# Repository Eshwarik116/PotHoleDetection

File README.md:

# Intelligent Pothole Detection System (IPDS)

An advanced IoT and AI-powered solution for real-time road hazard assessment using a dual ESP32 architecture and YOLOv8 object detection.

---

## Problem Statement
Poorly maintained roads and unexpected potholes cause severe vehicle damage and contribute to thousands of traffic accidents annually. Current road inspection methods rely heavily on slow, manual reporting by citizens or municipal workers, leaving prolonged periods where hazardous road conditions go unaddressed.

## Solution Overview
The IPDS project solves this by automating road quality assessment. By mounting a camera and accelerometer setup on a vehicle, the system continuously scans the road ahead. When the computer vision model detects a pothole, it triangulates that visual data with physical vibration data (jerk) captured as the vehicle drives over it. This creates a highly accurate, geo-tagged "Severity Score" for every pothole, ready to be mapped and prioritized by road maintenance authorities.

## Key Features
- **Real-time Pothole Detection:** Powered by a custom-trained YOLOv8 model.
- **Multi-Object Tracking:** Uses the SORT algorithm to prevent duplicate counting of the same pothole across frames.
- **Vehicle Vibration Sensing:** MPU6050 accelerometer accurately measures the physical depth/impact of the pothole.
- **GPS Location Tagging:** Automatically records the exact latitude and longitude of hazards.
- **Sensor Fusion Severity Scoring:** Combines AI visual confidence with physical impact data to rank pothole severity.
- **Smart Data Logging:** Outputs clean, Firebase-ready CSV logs.

---

## System Overview (High Level)
The system operates on an **Event-Driven Dual ESP32 Architecture**. 
1. The **ESP32-CAM** continuously streams video to a central Python processing hub.
2. The Python hub runs **YOLOv8** to visually detect potholes.
3. Upon confirming a valid pothole, Python sends a query to the **ESP32 Sensor Node**.
4. The Sensor Node responds with physical accelerometer, GPS, and RTC data.
5. The system calculates a combined severity score and logs the data.

## Hardware Used
- **Vision Node:** ESP32-CAM + OV2640 Module
- **Sensor Node:** ESP32 Dev Board
- **Accelerometer:** MPU6050 (6-axis motion tracking)
- **GPS Module:** NEO-6M
- **Real-Time Clock:** DS3231 RTC
- **Processing Hub:** Laptop or Edge Computer (e.g., Jetson Nano)

## Software Stack
- **Python 3.10+** (Core processing logic)
- **OpenCV** (Image processing and video stream handling)
- **Ultralytics YOLOv8** (Computer Vision / Object Detection)
- **FilterPy / SciPy** (SORT tracking algorithm)
- **C++ / Arduino Framework** (ESP32 Firmware)

---

## Project Structure
```text
Pot Hole Detection/
├── .env                             # Centralized WiFi credentials
├── README.md                        # This file
├── update_wifi.py                   # Script to inject WiFi credentials to C++
├── requirements.txt                 # Python dependencies
├── python/                          
│   ├── main.py                      # Main AI & Processing entry point
│   └── pothole_detection/           # SORT and YOLO wrapper modules
├── ESP_32_Code/                        
│   ├── esp_32_cam_final/            # ESP32-CAM firmware (Vision Node)
│   └── esp_32_final/                # ESP32 Sensor firmware (Sensor Node)
├── assets/
│   └── models/                      # Trained YOLOv8 model (.pt)
├── outputs/                         # Generated CSV logs and annotated videos
└── docs/                            # Deep technical documentation
```

---

## Installation & Setup Instructions

### 1. Hardware Configuration
1. Open the `.env` file in the root directory and update it with your WiFi Hotspot's SSID and Password. All devices *must* share the same network.
2. Run `python update_wifi.py` to sync these credentials to the ESP32 code.
3. Flash `ESP_32_Code/esp_32_cam_final/esp_32_cam_final.ino` to your ESP32-CAM. Monitor the Serial output to get its IP address.
4. Flash `ESP_32_Code/esp_32_final/esp_32_final.ino` to your ESP32 Sensor Node. Monitor the Serial output to get its IP address.

### 2. Software Configuration
1. Install dependencies: `pip install -r requirements.txt`
2. Open `python/main.py`.
3. Locate the `ESP32_CAM_IP` and `ESP32_SENSOR_IP` variables at the top of the file. Update them with the IPs you retrieved from the hardware step.

## Usage
To start the live tracking and detection system, simply run:
```bash
python python/main.py
```
A video window will open showing the live feed with bounding boxes and tracking IDs. Press `q` to safely terminate the program. All reports will be saved in the `outputs/logs/` directory.

---

## Future Scope
- **Dashcam Integration:** Utilize ubiquitous vehicle dashcams and smartphone apps to passively crowdsource road condition data without custom hardware.
- **System Scalability:** Migrate processing to distributed cloud infrastructure (AWS/GCP) using microservices and Kubernetes to handle millions of edge devices.
- **Government Portals:** Provide secure web dashboards for municipal bodies featuring real-time heatmaps and predictive analytics for budget allocation.
- **Navigational Alerts:** Integrate with OpenStreetMap (OSM) to issue proactive audio/visual warnings to drivers about upcoming road hazards.
- **Spatial Database:** Store detections in a highly optimized database (e.g., PostgreSQL with PostGIS) and expose REST APIs for researchers and self-driving models.
- **Advanced Sensor Integration:** Incorporate LiDAR or Thermal/Infrared cameras for 24/7 visibility regardless of weather, glare, or darkness.
- **Predictive Maintenance:** Analyze micro-cracks and freeze-thaw weather patterns to predict and map impending road failures before physical potholes form.
- **V2X Communication:** Broadcast real-time hazard coordinates to trailing autonomous vehicles so they can automatically steer around or brace for impact.
- **Automated Work-Orders:** Integrate strictly with City ERP software to automatically dispatch repair crews and calculate necessary asphalt volumes for severe hazards.
- **True Edge Acceleration:** Utilize dedicated AI ASICs (like Google Coral TPU or Hailo-8) to run the entire YOLO pipeline locally without needing a laptop.
- **Crowdsourcing Incentives:** Implement gamified "micro-bounties" (e.g., toll credits or tax rebates) to incentivize citizens to run the detection app while commuting.

## Contributors
- **Sanskar Tiwari** - *Core Architecture & ML Pipeline*

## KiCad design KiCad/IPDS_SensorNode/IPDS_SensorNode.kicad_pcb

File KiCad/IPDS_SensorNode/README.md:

# IPDS Sensor Node — KiCad PCB Project

**KiCad Version:** 7.x  
**Board:** 120 × 90 mm · FR4 · 1.6 mm · 2 layers · HASL · 1 oz copper

---

## Files in This Project

| File | Description |
|---|---|
| `IPDS_SensorNode.kicad_pro` | KiCad project settings & DRC rules |
| `IPDS_SensorNode.kicad_sch` | Full schematic — all components & nets |
| `IPDS_SensorNode.kicad_pcb` | PCB layout — footprints, traces, GND plane |
| `sym-lib-table` | Symbol library references |
| `fp-lib-table` | Footprint library references |

---

## How to Open

1. Install **KiCad 7** (https://www.kicad.org/download/)
2. Open `IPDS_SensorNode.kicad_pro` — KiCad will load the project
3. Open **Schematic Editor** (Eeschema) to view the schematic
4. Open **PCB Editor** (PcbNew) to view and edit the PCB layout

---

## Design Overview

### Components

| Ref | Value | Description | Footprint |
|---|---|---|---|
| J1 | ESP32_Left | ESP32 DevKit V1 Left 19-pin header | PinHeader_1x19_P2.54mm |
| J2 | ESP32_Right | ESP32 DevKit V1 Right 19-pin header | PinHeader_1x19_P2.54mm |
| J3 | MPU6050 | 3-Axis Accel+Gyro I²C module | PinHeader_1x06_P2.54mm |
| J4 | DS3231_RTC | TCXO RTC I²C module w/ CR2032 | PinHeader_1x04_P2.54mm |
| J5 | NEO-6M_GPS | u-blox GPS UART module | PinHeader_1x04_P2.54mm |
| J6 | USB_Micro_B | USB Micro-B power input (5V → VIN) | USB_Micro-B_Molex_47589 |
| R1 | 4.7 kΩ | SDA pull-up (I²C) | R_0402_1005Metric |
| R2 | 4.7 kΩ | SCL pull-up (I²C) | R_0402_1005Metric |
| C1 | 100 nF | 3.3V decoupling capacitor | C_0402_1005Metric |
| C2 | 10 µF | 3.3V bulk capacitor | C_0805_2012Metric |
| H1–H4 | M3 | PCB mounting holes (3.2 mm drill) | MountingHole_3.2mm_M3 |
| TP1–TP4 | — | Test points: +3V3, GND, SDA, SCL | TestPoint_Pad_1.0x1.0mm |

### Net List

| Net | Signal | Connected To |
|---|---|---|
| `+3V3` | 3.3V power | ESP32 3V3 pin → all VCC |
| `GND` | Ground | Common GND + B.Cu pour |
| `SDA` | I²C Data | GPIO21 ↔ MPU6050 SDA ↔ DS3231 SDA + R1 |
| `SCL` | I²C Clock | GPIO22 ↔ MPU6050 SCL ↔ DS3231 SCL + R2 |
| `GPS_TX` | UART2 RX in | NEO-6M TX → GPIO16 (RX2) |
| `GPS_RX` | UART2 TX out | GPIO17 (TX2) → NEO-6M RX |
| `VIN` | 5V from USB | USB VBUS → ESP32 VIN |

### I²C Addresses

| Device | Address |
|---|---|
| MPU6050 | `0x68` (AD0 = GND) |
| DS3231 | `0x57` (fixed) |

### UART Settings

| Parameter | Value |
|---|---|
| Port | UART2 |
| Baud rate | 9600 bps |
| Data bits | 8 |
| Parity | None |
| Stop bits | 1 |

---

## PCB Design Rules

| Rule | Value |
|---|---|
| Min trace width | 0.2 mm |
| Power trace width | 0.5 mm |
| Signal trace width | 0.25 mm |
| Min clearance | 0.2 mm |
| Via drill | 0.4 mm |
| Via diameter | 0.8 mm |
| Min hole-to-hole | 0.25 mm |
| Min copper-to-edge | 0.5 mm |
| Solder mask expansion | 0.05 mm |
| Board thickness | 1.6 mm |

---

## Gerber Export (for fabrication)

In KiCad PCB Editor:

1. **File → Fabrication Outputs → Gerbers (.gbr)**
2. Output directory: `Gerbers/`
3. Enable layers:
   - `F.Cu` (front copper)
   - `B.Cu` (back copper / GND plane)
   - `F.SilkS` (front silkscreen)
   - `B.SilkS` (back silkscreen)
   - `F.Mask` (front solder mask)
   - `B.Mask` (back solder mask)
   - `Edge.Cuts` (board outline)
4. **File → Fabrication Outputs → Drill Files (.drl)**
   - Format: Excellon
   - Origin: Absolute

### Recommended Fabs
- [JLCPCB](https://jlcpcb.com) — upload Gerbers zip
- [PCBWay](https://www.pcbway.com)
- [OSH Park](https://oshpark.com)

---

## BOM — Bill of Materials

| Qty | Ref | Value | MPN / Note |
|---|---|---|---|
| 1 | J1,J2 | ESP32 DevKit V1 | AI-Thinker / Random Nerd |
| 1 | J3 | MPU6050 Module | GY-521 breakout |
| 1 | J4 | DS3231 RTC Module | DS3231 breakout w/ CR2032 |
| 1 | J5 | NEO-6M GPS | u-blox NEO-6M module |
| 1 | J6 | USB Micro-B | Molex 47589-0001 |
| 2 | R1,R2 | 4.7 kΩ 0402 | Vishay CRCW04024K70FKED |
| 1 | C1 | 100 nF 0402 10V | Murata GRM155R71A104KA01D |
| 1 | C2 | 10 µF 0805 10V | Murata GRM21BR61A106KE18L |
| 4 | H1–H4 | M3 standoffs | 10 mm brass hex standoff |

---

## Notes

- **Power:** Feed 5V via USB Micro-B (J6) or directly to ESP32 `VIN`. ESP32 onboard AMS1117 regulates to 3.3V.
- **I²C pull-ups:** R1 and R2 are mandatory. Omitting them will cause unreliable I²C comms.
- **GPS antenna:** The NEO-6M module has an integrated ceramic patch antenna. Ensure no copper pours below it or use an active external antenna.
- **AD0 (MPU6050):** Tied to GND on the module, sets I²C address to `0x68`. If using two MPU6050s, tie AD0 of the second to 3.3V for address `0x69`.
- **After PCB modifications:** Re-run DRC (Design → Design Rules Checker) and re-generate netlist before Gerber export.

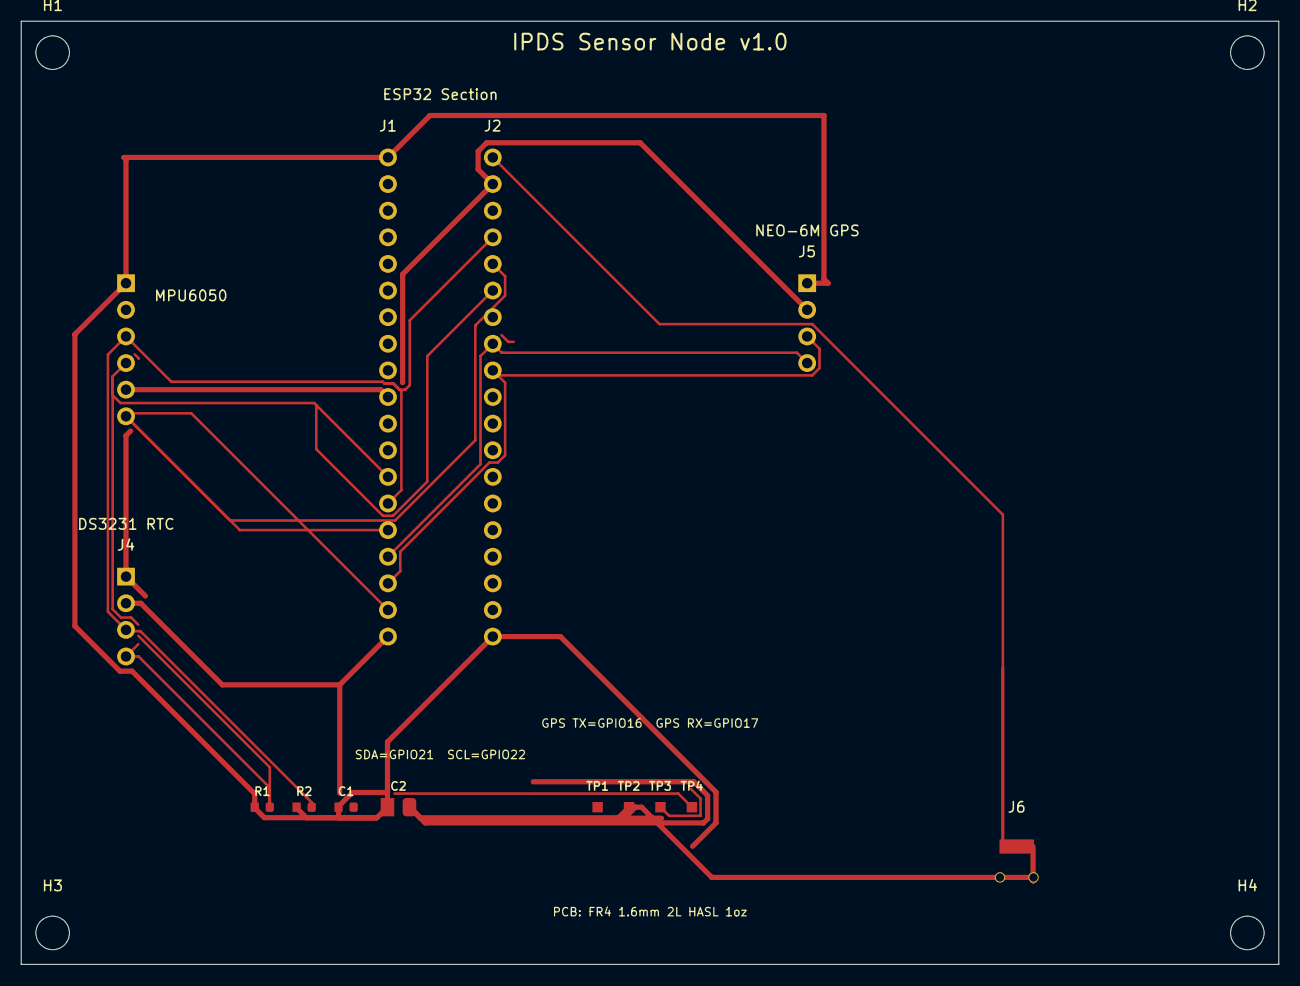
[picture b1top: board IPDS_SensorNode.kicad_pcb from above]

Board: 2 copper layers, 120.0 x 90.0 mm, 18 parts (0 on the bottom side), 7 nets.

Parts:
C1: 100nF; C_0402_1005Metric
C2: 10uF; C_0805_2012Metric
H1, H2, H3, H4: MountingHole_3.2mm_M3
J1: ESP32_Left; PinHeader_1x19_P2.54mm_Vertical
J2: ESP32_Right; PinHeader_1x19_P2.54mm_Vertical
J3: MPU6050; PinHeader_1x06_P2.54mm_Vertical
J4: DS3231_RTC; PinHeader_1x04_P2.54mm_Vertical
J5: NEO-6M_GPS; PinHeader_1x04_P2.54mm_Vertical
J6: USB_Micro_B; USB_Micro-B_Molex_47589-0001
R1, R2: 4.7k; R_0402_1005Metric
TP1: +3V3; TestPoint_Pad_1.0x1.0mm
TP2: GND; TestPoint_Pad_1.0x1.0mm
TP3: SDA; TestPoint_Pad_1.0x1.0mm
TP4: SCL; TestPoint_Pad_1.0x1.0mm

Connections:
+3V3: C1.1, C2.1, J1.1, J2.19, J3.1, J4.1, J5.1, R1.1, R2.1, TP1.1
GND: C1.2, C2.2, J1.10, J1.19, J2.2, J3.2, J3.5, J4.2, J5.2, J6.5, J6.MP, TP2.1
GPS_RX: J1.16, J2.8, J5.4
GPS_TX: J1.17, J2.9, J5.3
SCL: J1.14, J2.4, J3.3, J4.3, R2.2, TP4.1
SDA: J1.13, J2.6, J3.4, J4.4, R1.2, TP3.1
VIN: J2.1, J6.1

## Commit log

2026-02-04 added the ino files and fixed it
2026-02-10 updated the readme and .ino
2026-02-18 edited the ino file
2026-02-18 sample
2026-03-13 update scope of the project
2026-03-13 made flowchart and kicad files
2026-03-18 Implement NTP time sync for RTC
    Added NTP time synchronization for RTC initialization.
2026-03-31 bugs fixxed and csv fixed
2026-04-07 final commit
2026-04-08 Updated KiCad design - PCB and schematic improvements
2026-04-08 Updated KiCad design
